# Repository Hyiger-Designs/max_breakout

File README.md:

# MAX7000S Breakout Board
A breadboard and 5V TLL friendly CPLD breakout board

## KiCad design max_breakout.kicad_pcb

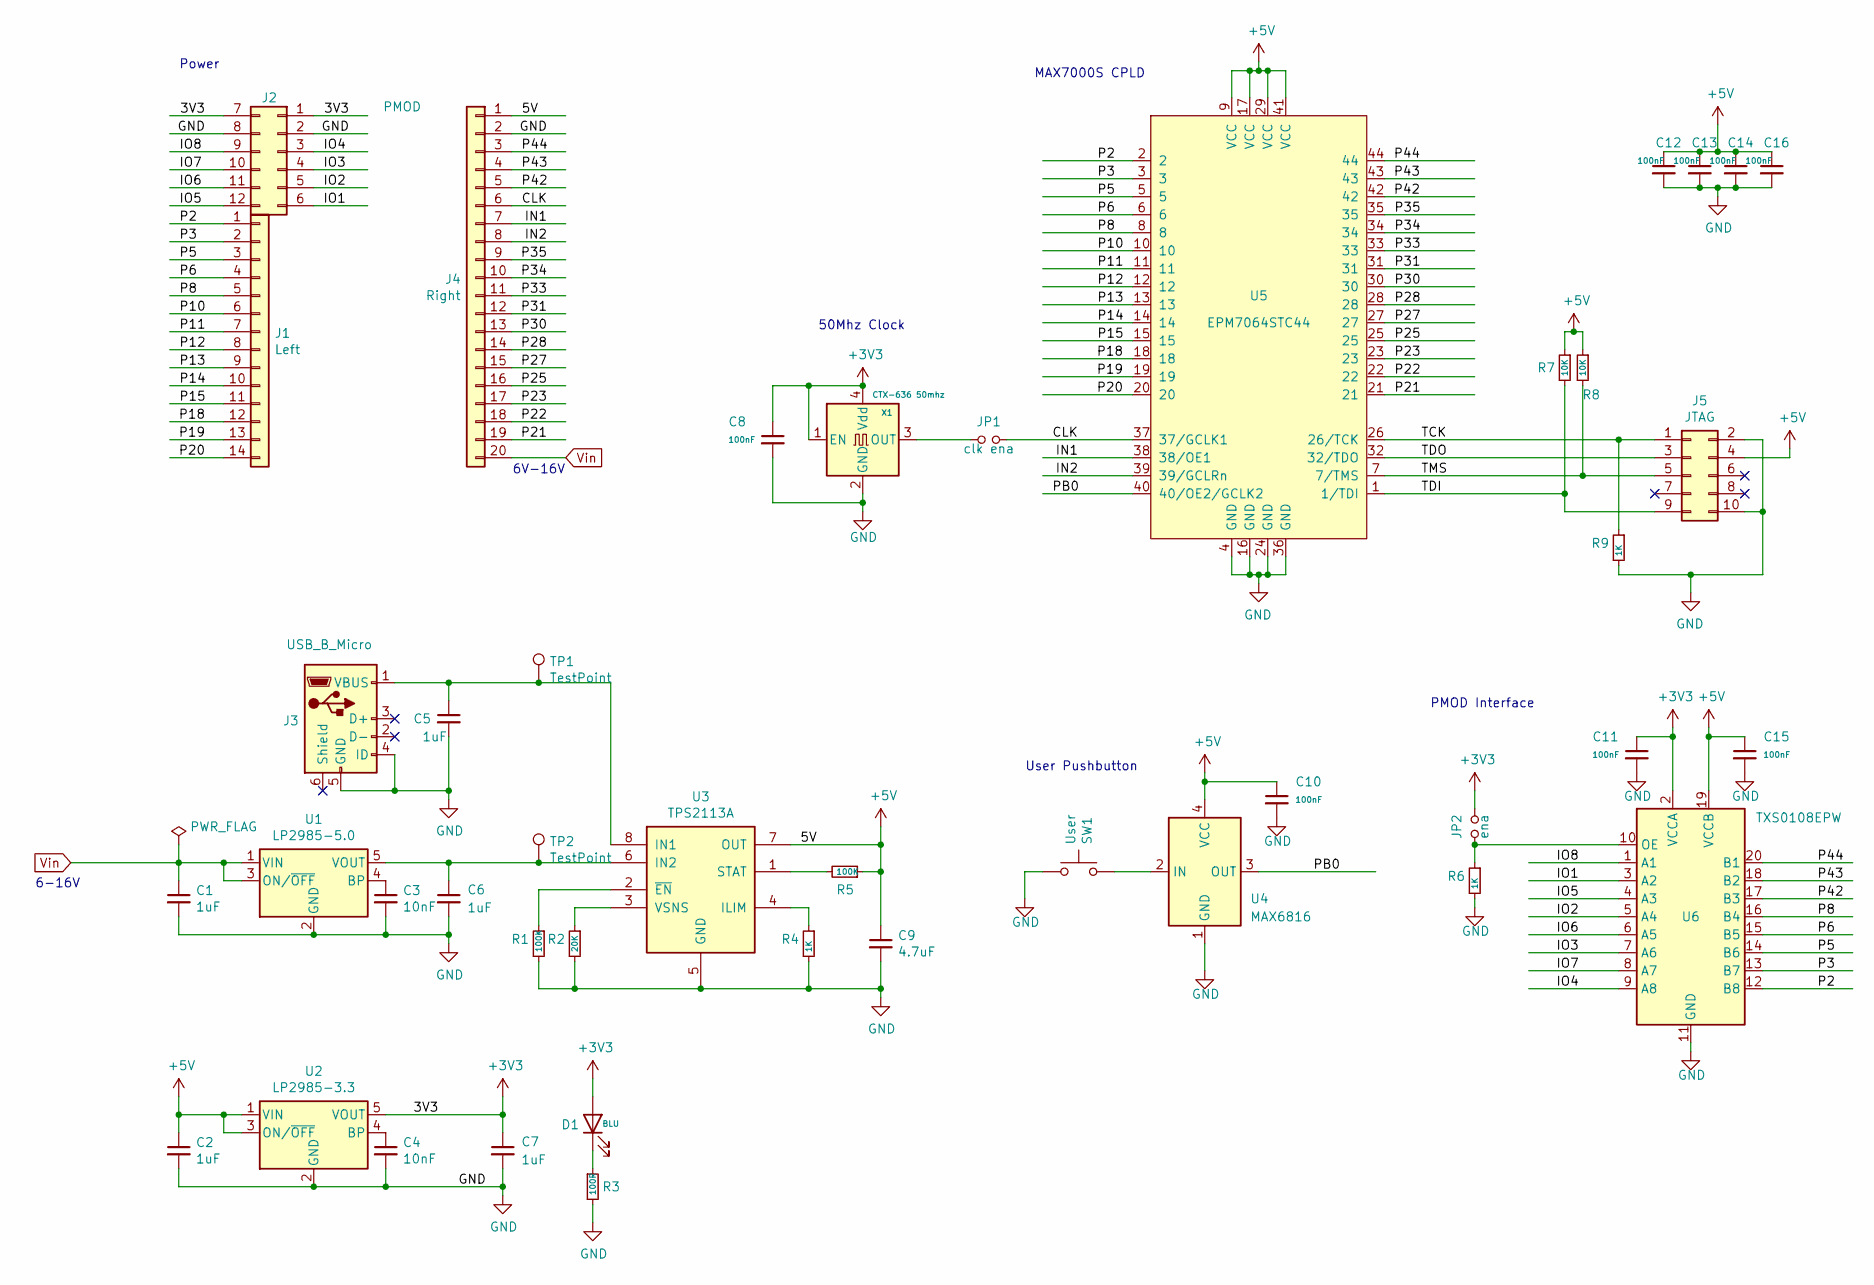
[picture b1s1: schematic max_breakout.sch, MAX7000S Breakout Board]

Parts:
C1, C2, C5, C6, C7: 1uF; C_0603_1608Metric_Pad1.08x0.95mm_HandSolder; MPN C0603C105K3PACTU
C3, C4: 10nF; C_0603_1608Metric_Pad1.05x0.95mm_HandSolder; MPN C0603C103J5RACTU
C8, C10, C11, C12, C13, C14, C15, C16: 100nF; C_0603_1608Metric_Pad1.08x0.95mm_HandSolder; MPN C0603C104J5RACTU
C9: 4.7uF; C_0603_1608Metric_Pad1.05x0.95mm_HandSolder; MPN C0603C475K8PACTU
D1: BLU; LED_0603_1608Metric_Pad1.05x0.95mm_HandSolder; MPN SMLD12BN1WT86
J1: Left; PinHeader_1x14_P2.54mm_Vertical
J2: PMOD; PinSocket_2x06_Top_Bottom_P2.54mm_Horizontal
J3: USB_B_Micro; USB_Micro-B_Amphenol_10103594-0001LF_Horizontal; MPN 10103594-0001LF
J4: Right; PinHeader_1x20_P2.54mm_Vertical
J5: JTAG; PinHeader_2x05_P2.54mm_Vertical
JP1: clk ena; PinHeader_1x02_P2.54mm_Vertical
JP2: ena; PinHeader_1x02_P2.54mm_Vertical
R1, R5: 100K; R_0603_1608Metric_Pad1.05x0.95mm_HandSolder; MPN CR0603-FX-1003ELF
R2: 20K; R_0603_1608Metric_Pad1.05x0.95mm_HandSolder; MPN CR0603-FX-2002ELF
R3: 100R; R_0603_1608Metric_Pad1.05x0.95mm_HandSolder; MPN CR0603-FX-1001ELF
R4, R6, R9: 1K; R_0603_1608Metric_Pad1.05x0.95mm_HandSolder; MPN CR0603-FX-1001ELF
R7, R8: 10K; R_0603_1608Metric_Pad1.05x0.95mm_HandSolder; MPN CR0603-FX-1002ELF
SW1: User; SW_Push_SPST_NO_Alps_SKRK; MPN SKRKAEE020
TP1, TP2: TestPoint; TestPoint_Pad_D1.5mm
U1: LP2985-5.0; SOT-23-5; MPN LP2985-50DBVR
U2: LP2985-3.3; SOT-23-5; MPN LP2985-33DBVR
U3: TPS2113A; TSSOP-8_4.4x3mm_P0.65mm; MPN TPS2113APWR
U4: MAX6816; SOT-143; MPN MAX6816EUS+T
U5: EPM7064STC44; TQFP-44_10x10mm_P0.8mm; MPN EPM7064STC44-10N
U6: TXS0108EPW; TSSOP-20_4.4x6.5mm_P0.65mm; MPN TXS0108EPWR
X1: CTX-636 50mhz; Oscillator_SMD_TXC_7C-4Pin_5.0x3.2mm_HandSoldering; MPN 636L3C050M00000

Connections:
+3V3: C7.1, C8.1, C11.1, D1.2 (A), J2.1, J2.7, JP2.2, U2.5 (VOUT), U6.2 (VCCA), X1.1 (EN), X1.4 (Vdd)
+5V: C2.1, C9.1, C10.1, C12.1, C13.1, C14.1, C15.1, C16.1, J4.1, J5.4, R5.1, R7.1, R8.1, U2.1 (VIN), U2.3 (ON/~OFF~), U3.7 (OUT), U4.4 (VCC), U5.9 (VCC), U5.17 (VCC), U5.29 (VCC), U5.41 (VCC), U6.19 (VCCB)
/CLK: J4.6, JP1.1, U5.37 (37/GCLK1)
/IN1: J4.7, U5.38 (38/OE1)
/IN2: J4.8, U5.39 (39/GCLRn)
/IO1: J2.6, U6.3 (A2)
/IO2: J2.5, U6.5 (A4)
/IO3: J2.4, U6.7 (A6)
/IO4: J2.3, U6.9 (A8)
/IO5: J2.12, U6.4 (A3)
/IO6: J2.11, U6.6 (A5)
/IO7: J2.10, U6.8 (A7)
/IO8: J2.9, U6.1 (A1)
/P2: J1.1, U5.2, U6.12 (B8)
/P3: J1.2, U5.3, U6.13 (B7)
/P5: J1.3, U5.5, U6.14 (B6)
/P6: J1.4, U5.6, U6.15 (B5)
/P8: J1.5, U5.8, U6.16 (B4)
/P10: J1.6, U5.10
/P11: J1.7, U5.11
/P12: J1.8, U5.12
/P13: J1.9, U5.13
/P14: J1.10, U5.14
/P15: J1.11, U5.15
/P18: J1.12, U5.18
/P19: J1.13, U5.19
/P20: J1.14, U5.20
/P21: J4.19, U5.21
/P22: J4.18, U5.22
/P23: J4.17, U5.23
/P25: J4.16, U5.25
/P27: J4.15, U5.27
/P28: J4.14, U5.28
/P30: J4.13, U5.30
/P31: J4.12, U5.31
/P33: J4.11, U5.33
/P34: J4.10, U5.34
/P35: J4.9, U5.35
/P42: J4.5, U5.42, U6.17 (B3)
/P43: J4.4, U5.43, U6.18 (B2)
/P44: J4.3, U5.44, U6.20 (B1)
/PB0: U4.3 (OUT), U5.40 (40/OE2/GCLK2)
/TCK: J5.1, R9.1, U5.26 (26/TCK)
/TDI: J5.9, R7.2, U5.1 (1/TDI)
/TDO: J5.3, U5.32 (32/TDO)
/TMS: J5.5, R8.2, U5.7 (7/TMS)
GND: C1.2, C2.2, C3.2, C4.2, C5.2, C6.2, C7.2, C8.2, C9.2, C10.2, C11.2, C12.2, C13.2, C14.2, C15.2, C16.2, J2.2, J2.8, J3.4 (ID), J3.5 (GND), J4.2, J5.2, J5.10, R1.2, R2.2, R3.2, R4.2, R6.2, R9.2, SW1.2, U1.2 (GND), U2.2 (GND), U3.5 (GND), U4.1 (GND), U5.4 (GND), U5.16 (GND), U5.24 (GND), U5.36 (GND), U6.11 (GND), X1.2 (GND)
unnamed: C3.1, U1.4 (BP)
unnamed: C4.1, U2.4 (BP)
unnamed: C5.1, J3.1 (VBUS), TP1.1, U3.8 (IN1)
unnamed: C6.1, TP2.1, U1.5 (VOUT), U3.6 (IN2)
unnamed: D1.1 (K), R3.1
unnamed: JP1.2, X1.3 (OUT)
unnamed: JP2.1, R6.1, U6.10 (OE)
unnamed: R1.1, U3.2 (~EN)
unnamed: R2.1, U3.3 (VSNS)
unnamed: R4.1, U3.4 (ILIM)
unnamed: R5.2, U3.1 (STAT)
unnamed: SW1.1, U4.2 (IN)
Vin: C1.1, J4.20, U1.1 (VIN), U1.3 (ON/~OFF~)

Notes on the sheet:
User Pushbutton
50Mhz Clock
MAX7000S CPLD
Power
6-16V
6V-16V
PMOD Interface

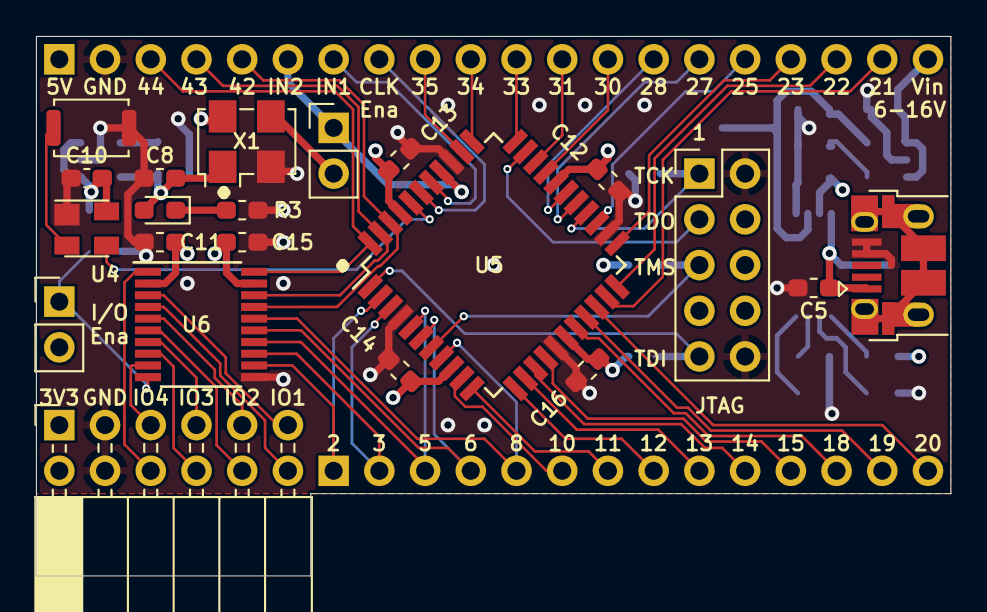
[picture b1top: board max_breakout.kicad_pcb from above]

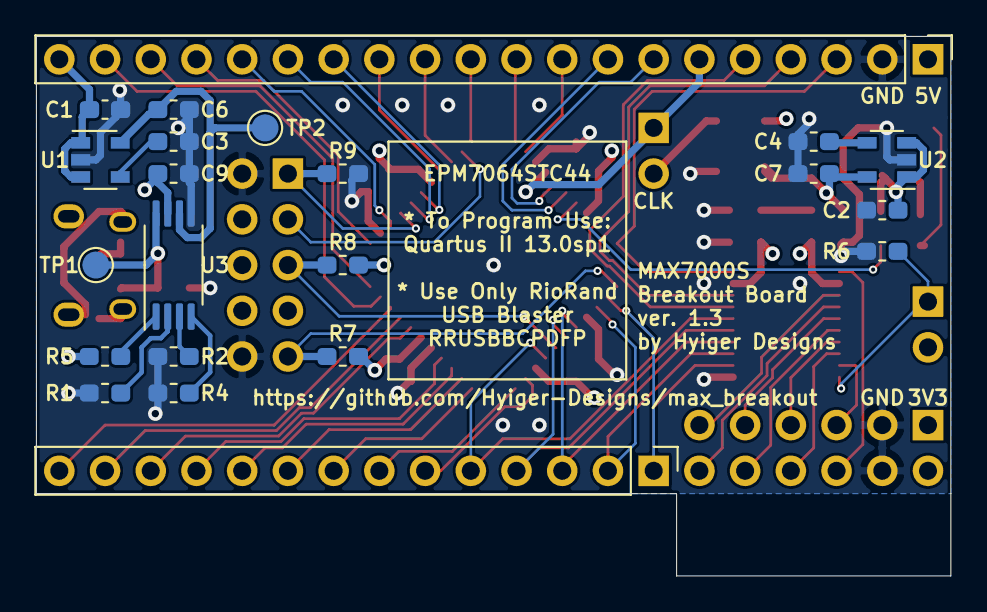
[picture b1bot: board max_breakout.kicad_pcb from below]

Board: 4 copper layers, 50.8 x 30.0 mm, 43 parts (22 on the bottom side), 60 nets.

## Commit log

2019-07-19 initial version
2019-07-20 switched to 32pins
2019-07-21 reorganized parts
2019-07-21 removed mac files
2019-07-21 removed bus
2019-07-22 added voltage stepdown for xtal
2019-07-24 finished layout
2019-07-24 checkpoint
2019-07-24 start routing
2019-07-25 version 1.0
2019-07-28 added docs
2019-07-29 cropped images
2019-07-29 replaced led with ldo regulator
2019-07-29 added reset and user push buttons
2019-07-30 docs, images and gerbers
2019-07-30 changed layout
2019-07-30 routed
2019-07-30 version 1.1
2019-07-30 Updated gerbers
2019-07-31 fixed up gnd planes
2019-07-31 cleanup
2019-08-25 fixed 3.3v reg pinouts, added thermal vias
2019-08-27 rerouted and updated BOM
2019-08-27 Fixed up library references
2019-08-27 changed field references
2019-08-28 fixed jtag pin, pull oe1 high
2019-08-28 fixed buffer layout
2019-08-29 fixed design rules. rerouting for noise reductions
2019-08-29 changed 20pin headers
2019-08-30 new routing and gnd plane
2019-08-30 more routing
2019-08-30 updated routing and gerbers
2019-08-31 fixed dip switch footprints, separated component vcc's
2019-09-01 better part alignment
2019-09-01 aligned traces
2019-09-03 version 2.0
2019-09-09 straighten traces
2019-09-24 fixed gnd plane breaks
2019-09-24 removed TDO pull-up, added JTAG bypass
2019-09-26 Added 5V and 3V3 regulators. Fixed USB GND issue
2019-09-26 redo
2019-09-26 do over
2019-09-26 realigned parts
2019-09-27 routing
2019-09-30 fixed ground breaks
2019-10-09 reorganized part layout, replace mosfet with inverter
2019-10-10 track cleanup
2019-10-15 removed switches
2019-10-16 finished routing
2019-10-17 fixed gnd breaks
2019-10-18 stuff
2019-12-29 removed extra cap from reg outputs
2020-05-08 Replaced RGB with leds. Reorganized switches. pulldowns for OE and RST
2020-05-08 smaller footprint for IC2, fixed thermal vias
2020-05-09 fixed silkscreen, added gnd thermal reliefs
2020-05-09 added open-drain clock driver, pull-ups for JTAG, removed TDI led
2020-05-09 fixed layout of regulators
2020-05-09 added level shifter on clock
2020-05-10 removed extraneous pullups
2020-05-10 rewired pushbuttons to input pins
2020-05-10 fixed unconnected errors
2020-05-10 switches push buttons and leds to active high, silk screen enhancements
2020-05-10 schematic cleanup
2020-05-10 fixed silkscreen
2020-05-11 tweaked silkscreen
2020-05-13 made USB shield a NC, add nofill region around xtal
2020-05-14 Added power mux, removed pb1
2020-05-15 changes to gnd plane and keepout areas
2020-05-15 added ferrite bead
2020-05-27 added TDI pullup
2020-05-27 cleaned up silkscreen and traces
2020-08-05 Added thermal reliefs
2020-08-10 replace jtag with standard connector
2020-08-10 silkscreen fixes, component layout
2020-08-20 Added pmod
2020-08-20 Reorganized pins
2020-08-21 added pmod connector
2020-08-22 removed leds, added full pmod
2020-08-22 replaced level translator with push-pull version
2020-08-25 added gnd and input pins
2020-08-28 Silkscreen adjustments
2020-09-04 flipped some components to front-side
2020-09-07 reorganized 3v3 parts
2020-09-07 consolidated pwr supply
2020-09-08 silkscreen updates
2020-09-23 corrected pin names, simplified PCB
2020-09-23 initial VHDL source for LED pmod
2020-10-03 added clock and uart VHDL projects
2020-10-03 rotated FPGA, reassigned pins
2020-10-26 added back led_pmod
2021-01-24 Simplified power supply
2021-02-06 reorganized 3V3 pwr
2021-03-13 Test points and silkscreen improvements
